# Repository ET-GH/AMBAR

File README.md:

# AMBAR
The software and hardware of the AMBAR project

Utilized Firmware includes all the logic used for our system.

Measurement & Control includes logic and API used for the measurement and control of the system. Airbrake.c includes references to a tmc5240 driver. Utilized Firmware has the completed driver but if your system used something else then changes must be made in the airbrake logic.

Communication includes logic and api used for communication and data between the flight computer and ground station. radio_bridge includes references to an sx1280 driver. Utilized Firmware has the completed driver but if your system used something else then changes must be made in the bridge logic. usb_comm includes references to the STM32 USB drivers. Utilized Firmware has the completed driver but if your system used something else then changes must be made in the usb logic.

GroundStation includes all the files used for qt application. Qt libraries were used for each of the integration files. The architecture can still be used if you don't want to use QT but the function calls will not work without the installed QT libraries.

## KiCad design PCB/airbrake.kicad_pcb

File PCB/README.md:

# AMBAR Flight Computer PCB
What we used for our project. You can buy all the components off of JLCPCB and Digikey

Export the gerber files and the bill of materials. Purchase the electrical componetns from digikey if you plan to solder but it's much easier to simply ask JLCPCB to fabricate and assemble the board.

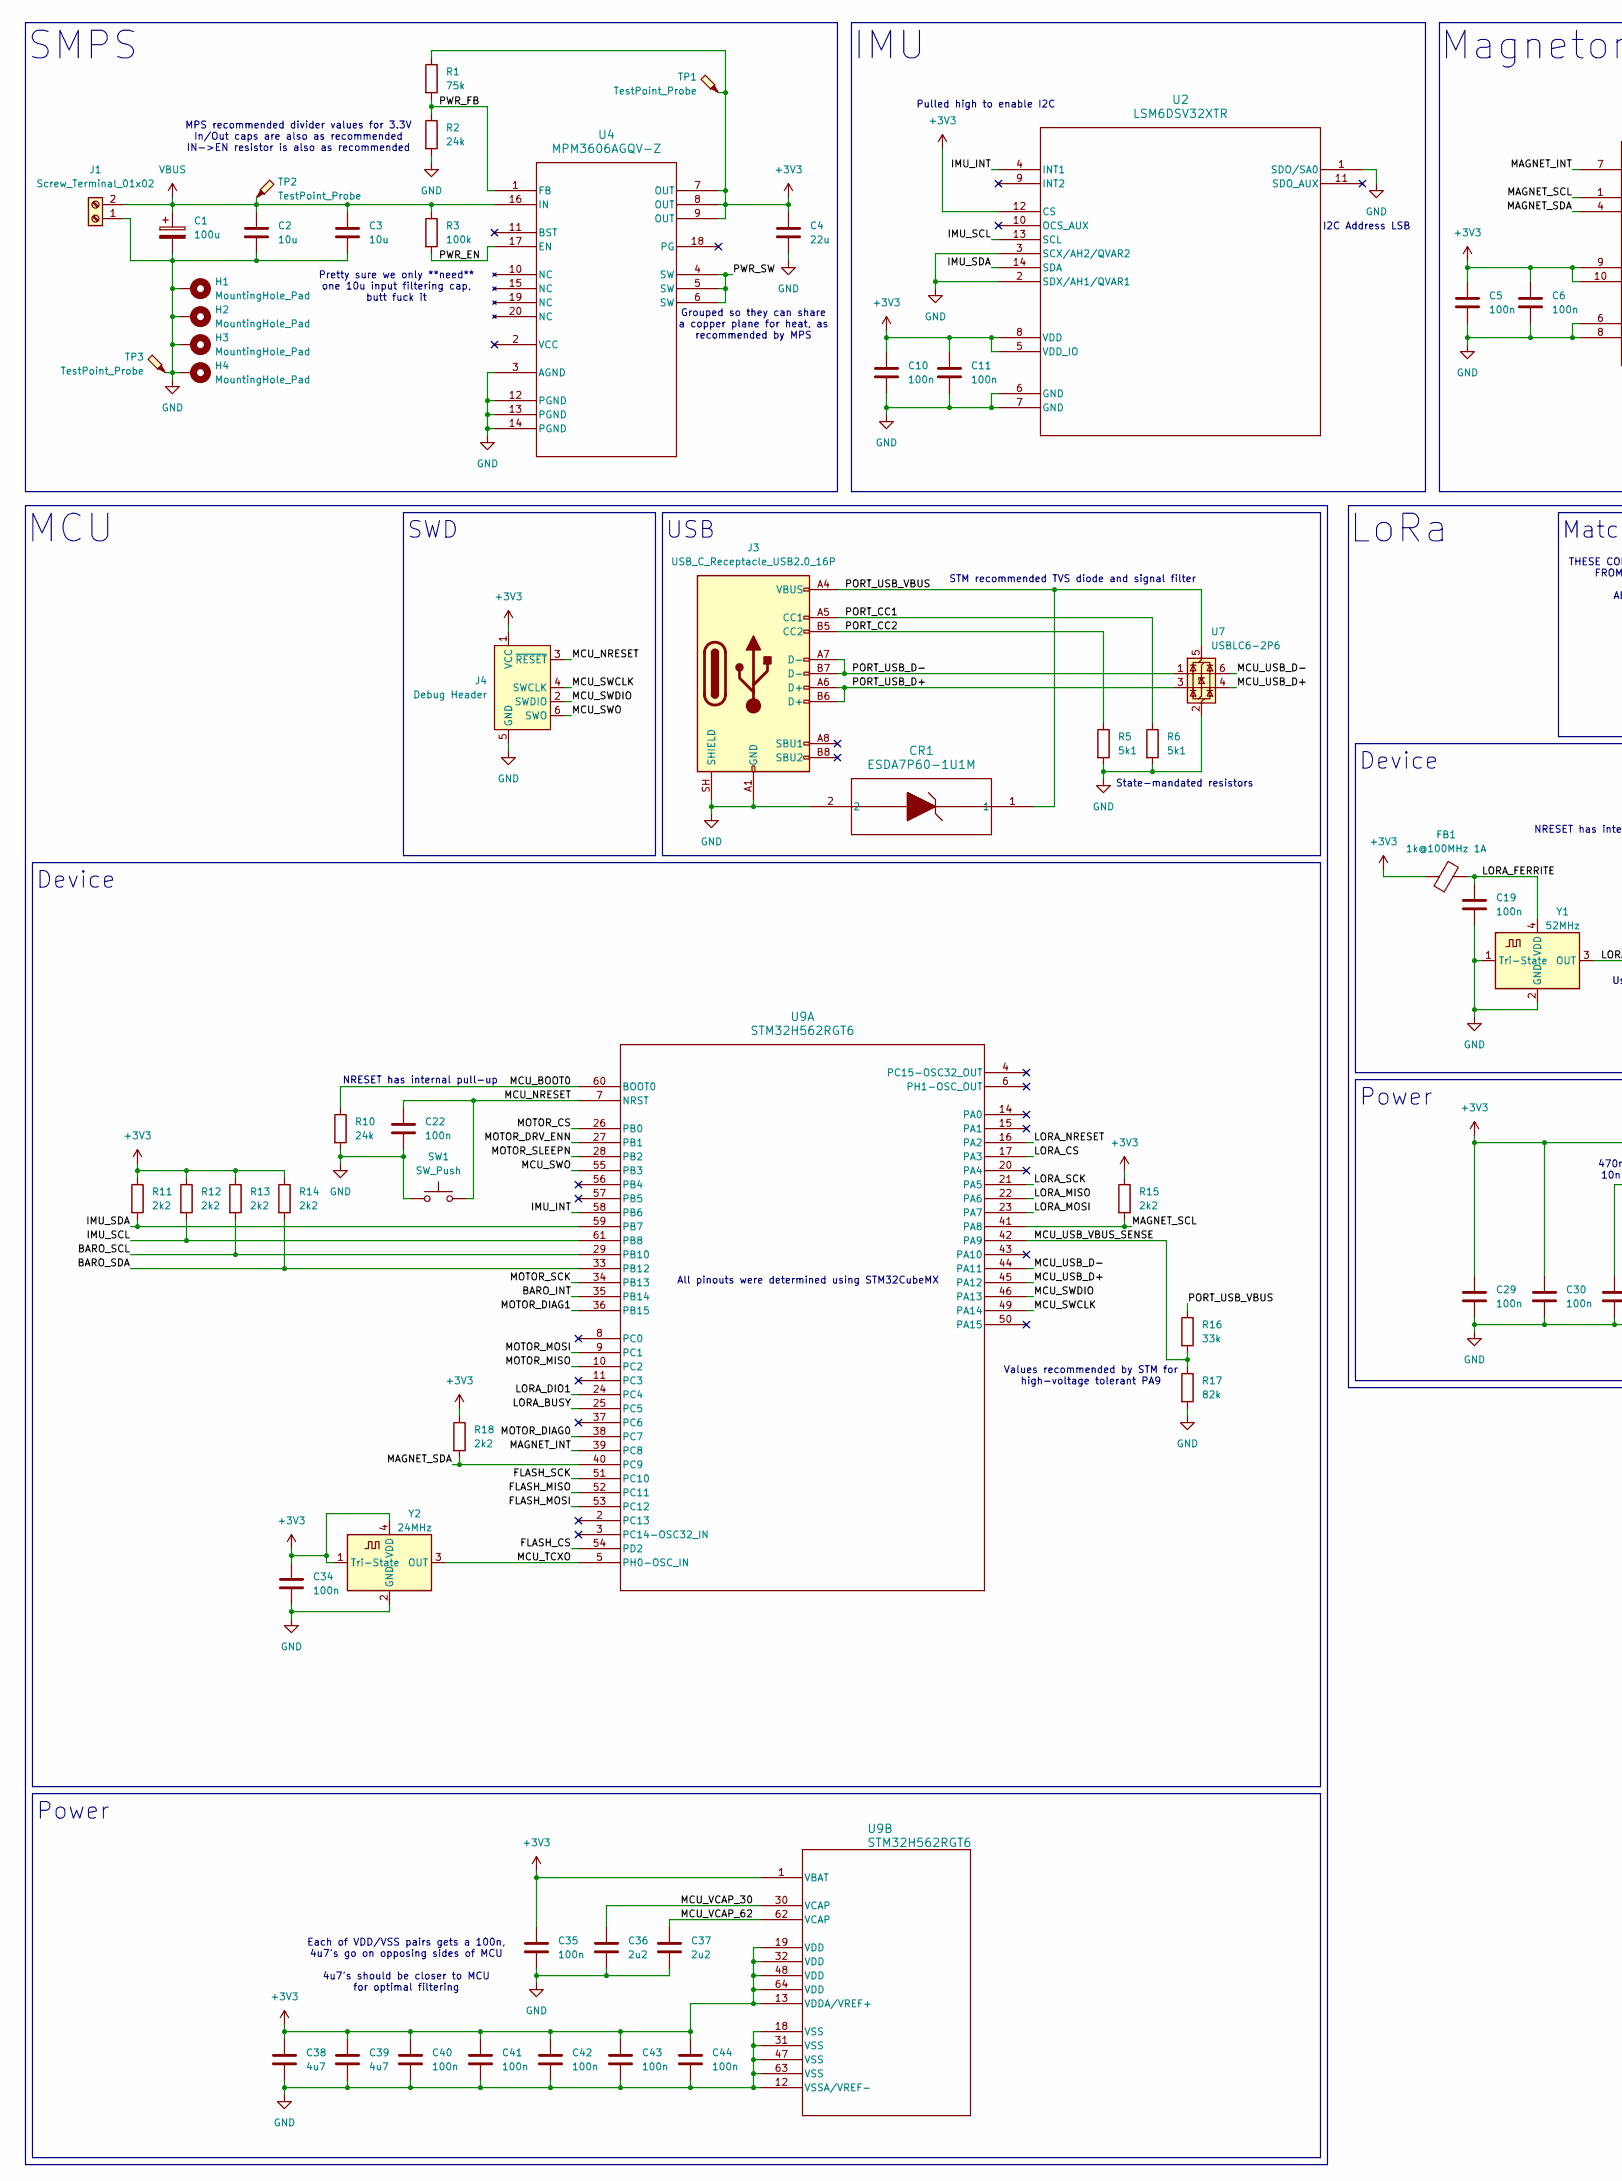
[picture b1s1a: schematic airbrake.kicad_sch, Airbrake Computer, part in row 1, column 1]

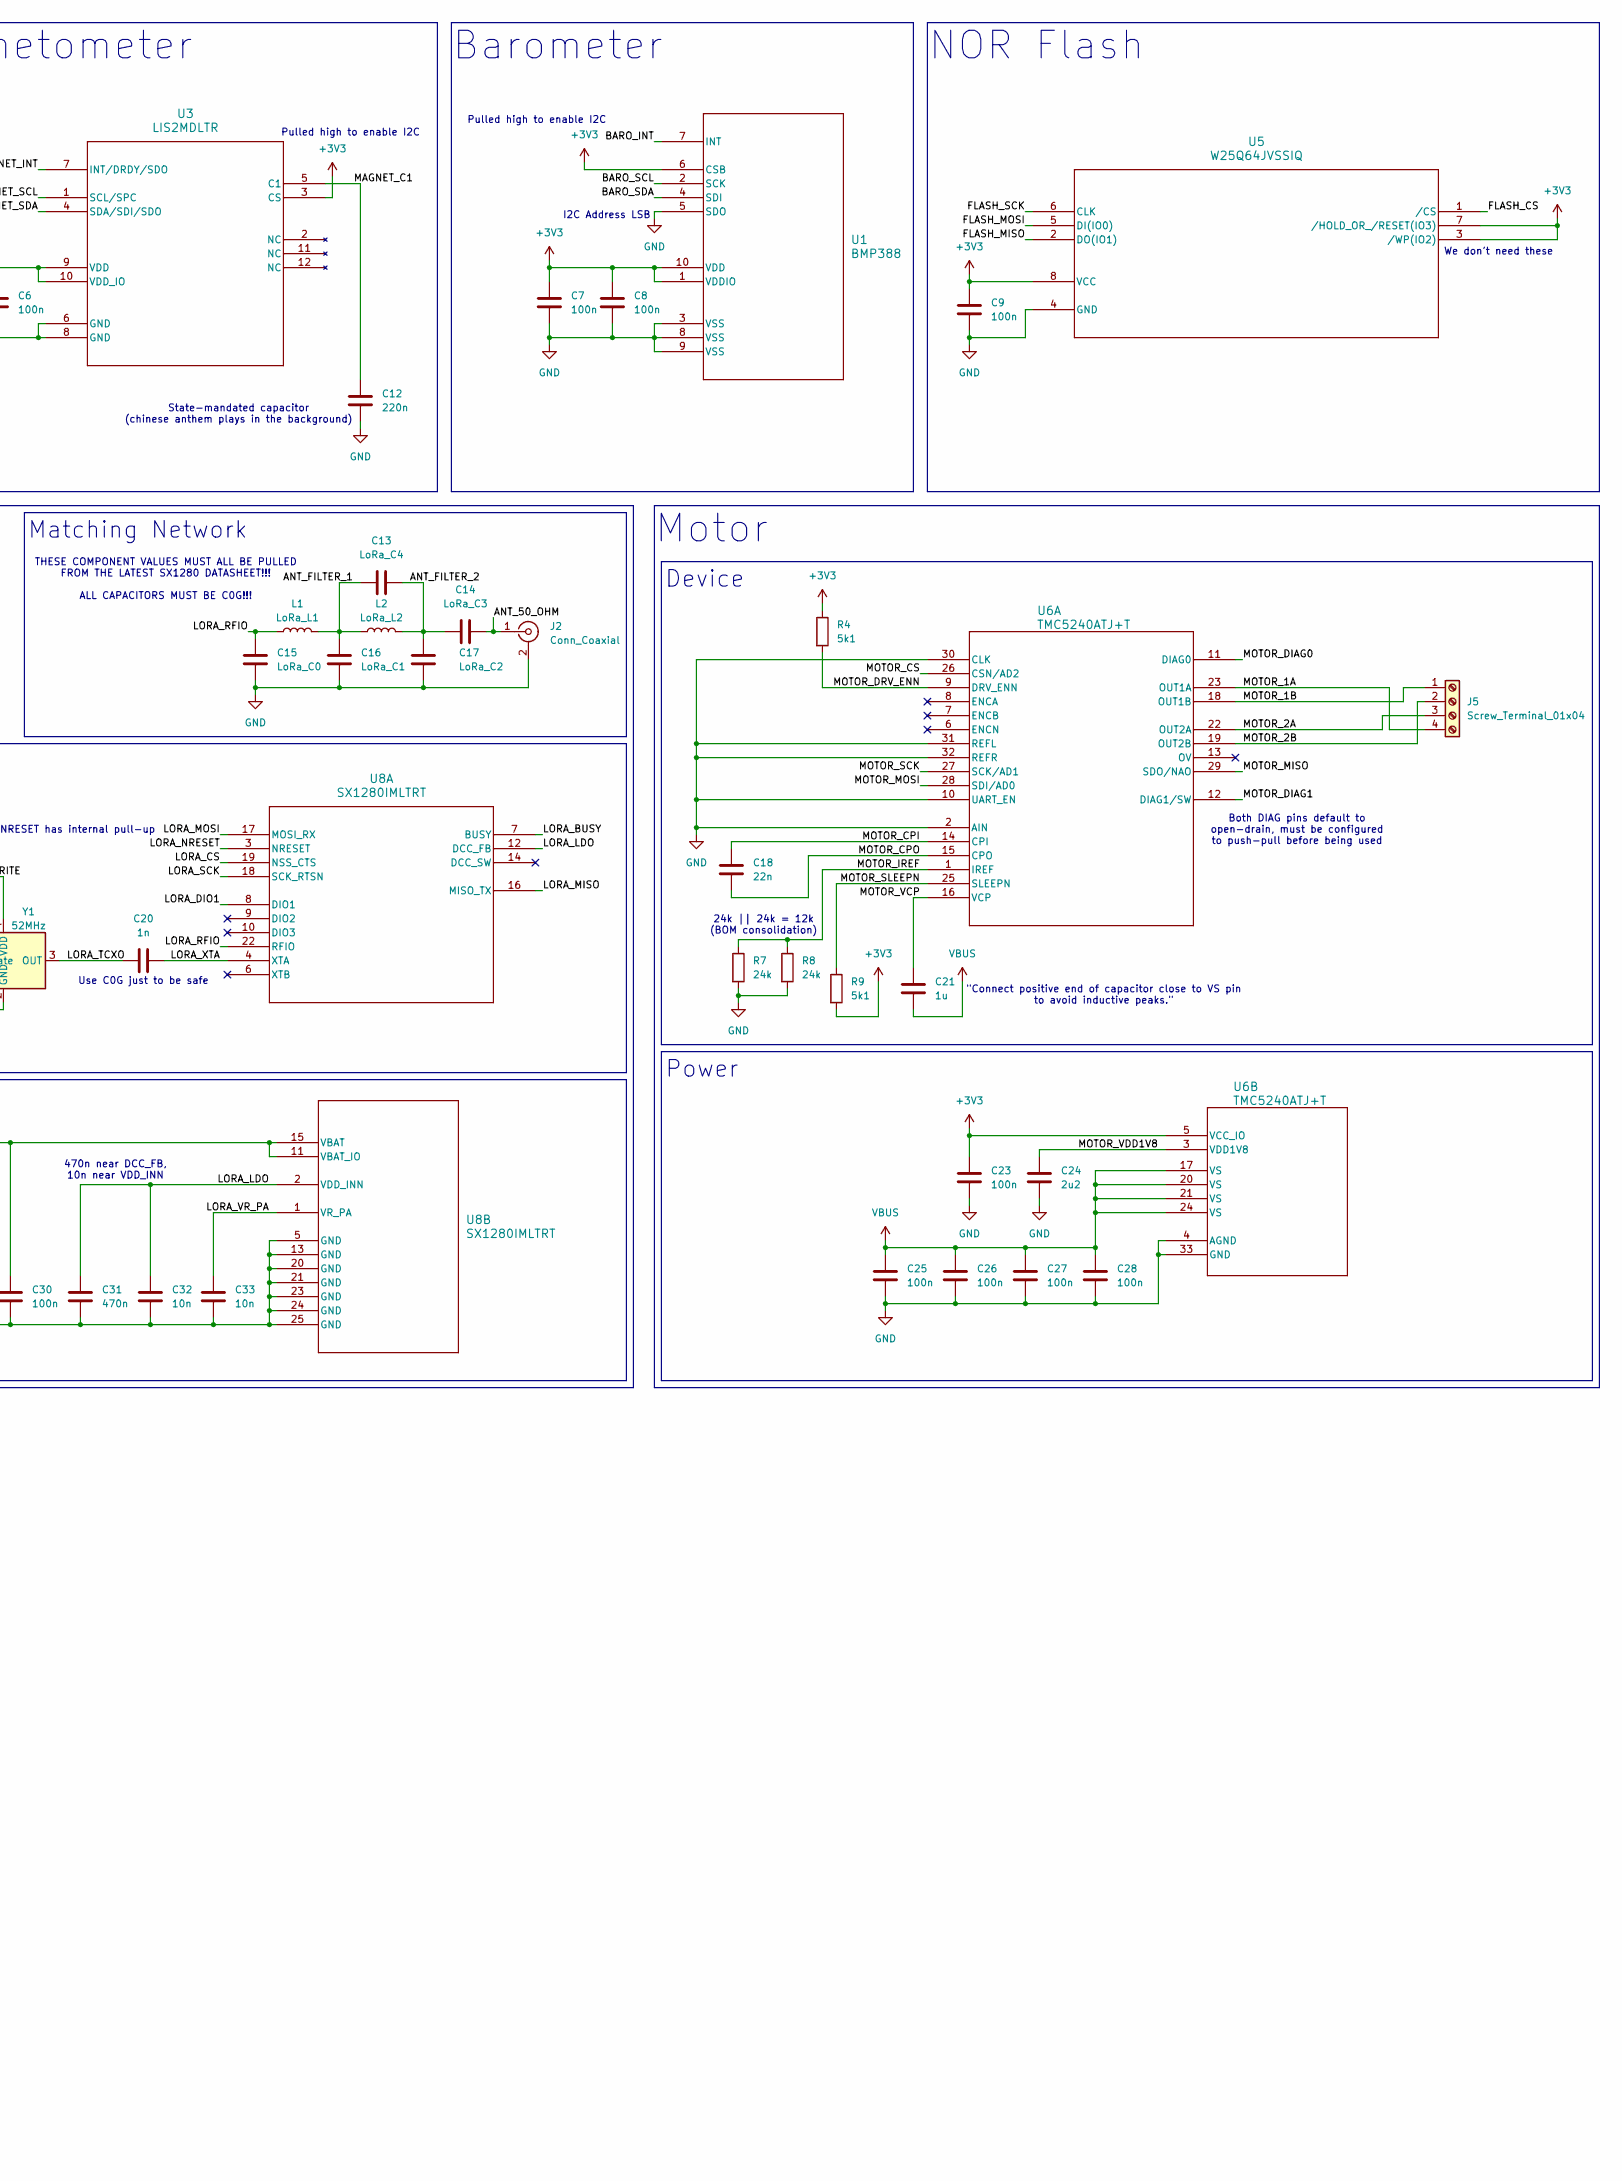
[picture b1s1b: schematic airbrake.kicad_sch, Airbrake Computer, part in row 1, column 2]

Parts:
C1: 100u; CP_Elec_6.3x7.7
C2, C3: 10u; C_0603_1608Metric
C4: 22u; C_0603_1608Metric
C5, C6, C7, C8, C9, C10, C11, C19, C22, C23, C25, C26, C27, C28, C29, C30, C34, C35, C40, C41, C42, C43, C44: 100n; C_0402_1005Metric
C12: 220n; C_0402_1005Metric
C13: LoRa_C4; C_0402_1005Metric
C14: LoRa_C3; C_0402_1005Metric
C15: LoRa_C0; C_0402_1005Metric
C16: LoRa_C1; C_0402_1005Metric
C17: LoRa_C2; C_0402_1005Metric
C18: 22n; C_0402_1005Metric
C20: 1n; C_0402_1005Metric
C21: 1u; C_0402_1005Metric
C24, C36, C37: 2u2; C_0402_1005Metric
C31: 470n; C_0402_1005Metric
C32, C33: 10n; C_0402_1005Metric
C38, C39: 4u7; C_0402_1005Metric
CR1: ESDA7P60-1U1M; ZDO_1610_STM
FB1: 1k@100MHz 1A; L_0603_1608Metric
H1, H2, H3, H4: MountingHole_Pad; MountingHole_2.2mm_M2_Pad_Via
J1: Screw_Terminal_01x02; TerminalBlock_Xinya_XY308-2.54-2P_1x02_P2.54mm_Horizontal
J2: Conn_Coaxial; U.FL_Hirose_U.FL-R-SMT-1_Vertical
J3: USB_C_Receptacle_USB2.0_16P; USB_C_Receptacle_GCT_USB4105-xx-A_16P_TopMnt_Horizontal
J4: Debug Header; Tag-Connect_TC2030-IDC-NL_2x03_P1.27mm_Vertical
J5: Screw_Terminal_01x04; TerminalBlock_Xinya_XY308-2.54-4P_1x04_P2.54mm_Horizontal
L1: LoRa_L1; L_0402_1005Metric
L2: LoRa_L2; L_0402_1005Metric
R1: 75k; R_0402_1005Metric
R2, R7, R8, R10: 24k; R_0402_1005Metric
R3: 100k; R_0402_1005Metric
R4, R5, R6, R9: 5k1; R_0402_1005Metric
R11, R12, R13, R14, R15, R18: 2k2; R_0402_1005Metric
R16: 33k; R_0402_1005Metric
R17: 82k; R_0402_1005Metric
SW1: SW_Push; SW_SPST_B3U-1000P
TP1, TP2, TP3: TestPoint_Probe; TestPoint_Pad_D2.5mm
U1: BMP388; QFN_BMP388_BOS
U2: LSM6DSV32XTR; LGA-14L_2p5X3p0X0p86_STM
U3: LIS2MDLTR; LGA-12_2X2X1_STM
U4: MPM3606AGQV-Z; QFN3p0x5p0x1p6_MPM3606A_MNP
U5: W25Q64JVSSIQ; SOIC-8_5P28X5P28_WIN-L
U6: TMC5240ATJ+T; 21-0140_T3255&plus_5C_ADI-L
U7: USBLC6-2P6; SOT-666
U8: SX1280IMLTRT; QFN24_4X4_SEM-L
U9: STM32H562RGT6; LQFP64-10x10mm_STM
Y1: 52MHz; Crystal_SMD_2016-4Pin_2.0x1.6mm
Y2: 24MHz; Crystal_SMD_2520-4Pin_2.5x2.0mm

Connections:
+3V3: C4.1, C5.1, C6.1, C7.1, C8.1, C9.1, C10.1, C11.1, C23.1, C29.1, C30.1, C34.1, C35.1, C38.1, C39.1, C40.1, C41.1, C42.1, C43.1, C44.1, FB1.1, J4.1 (VCC), R1.1, R4.1, R9.2, R11.1, R12.1, R13.1, R14.1, R15.1, R18.1, TP1.1 (1_1), U1.1 (VDDIO), U1.6 (CSB), U1.10 (VDD), U2.5 (VDD_IO), U2.8 (VDD), U2.12 (CS), U3.3 (CS), U3.9 (VDD), U3.10 (VDD_IO), U4.7 (OUT), U4.8 (OUT), U4.9 (OUT), U5.3 (/WP(IO2)), U5.7 (/HOLD_OR_/RESET(IO3)), U5.8 (VCC), U6.5 (VCC_IO), U8.11 (VBAT_IO), U8.15 (VBAT), U9.1 (VBAT), U9.13 (VDDA/VREF+), U9.19 (VDD), U9.32 (VDD), U9.48 (VDD), U9.64 (VDD), Y2.1 (Tri-State), Y2.4 (VDD)
/ANT_50_OHM: C14.2, J2.1 (In)
/ANT_FILTER_1: C13.1, C16.1, L1.2, L2.1
/ANT_FILTER_2: C13.2, C14.1, C17.1, L2.2
/BARO_INT: U1.7 (INT), U9.35 (PB14)
/BARO_SCL: R13.2, U1.2 (SCK), U9.29 (PB10)
/BARO_SDA: R14.2, U1.4 (SDI), U9.33 (PB12)
/FLASH_CS: U5.1 (/CS), U9.54 (PD2)
/FLASH_MISO: U5.2 (DO(IO1)), U9.52 (PC11)
/FLASH_MOSI: U5.5 (DI(IO0)), U9.53 (PC12)
/FLASH_SCK: U5.6 (CLK), U9.51 (PC10)
/IMU_INT: U2.4 (INT1), U9.58 (PB6)
/IMU_SCL: R12.2, U2.13 (SCL), U9.61 (PB8)
/IMU_SDA: R11.2, U2.14 (SDA), U9.59 (PB7)
/LORA_BUSY: U8.7 (BUSY), U9.25 (PC5)
/LORA_CS: U8.19 (NSS_CTS), U9.17 (PA3)
/LORA_DIO1: U8.8 (DIO1), U9.24 (PC4)
/LORA_FERRITE: C19.1, FB1.2, Y1.4 (VDD)
/LORA_LDO: C31.1, C32.1, U8.2 (VDD_INN), U8.12 (DCC_FB)
/LORA_MISO: U8.16 (MISO_TX), U9.22 (PA6)
/LORA_MOSI: U8.17 (MOSI_RX), U9.23 (PA7)
/LORA_NRESET: U8.3 (NRESET), U9.16 (PA2)
/LORA_RFIO: C15.1, L1.1, U8.22 (RFIO)
/LORA_SCK: U8.18 (SCK_RTSN), U9.21 (PA5)
/LORA_TCXO: C20.1, Y1.3 (OUT)
/LORA_VR_PA: C33.1, U8.1 (VR_PA)
/LORA_XTA: C20.2, U8.4 (XTA)
/MAGNET_C1: C12.1, U3.5 (C1)
/MAGNET_INT: U3.7 (INT/DRDY/SDO), U9.39 (PC8)
/MAGNET_SCL: R15.2, U3.1 (SCL/SPC), U9.41 (PA8)
/MAGNET_SDA: R18.2, U3.4 (SDA/SDI/SDO), U9.40 (PC9)
/MCU_BOOT0: R10.1, U9.60 (BOOT0)
/MCU_NRESET: C22.1, J4.3 (~RESET), SW1.2, U9.7 (NRST)
/MCU_SWCLK: J4.4 (SWCLK), U9.49 (PA14)
/MCU_SWDIO: J4.2 (SWDIO), U9.46 (PA13)
/MCU_SWO: J4.6 (SWO), U9.55 (PB3)
/MCU_TCXO: U9.5 (PH0-OSC_IN), Y2.3 (OUT)
/MCU_USB_D+: U7.4 (I/O2), U9.45 (PA12)
/MCU_USB_D-: U7.6 (I/O1), U9.44 (PA11)
/MCU_USB_VBUS_SENSE: R16.2, R17.1, U9.42 (PA9)
/MCU_VCAP_30: C36.1, U9.30 (VCAP)
/MCU_VCAP_62: C37.1, U9.62 (VCAP)
/MOTOR_1A: J5.4, U6.23 (OUT1A)
/MOTOR_1B: J5.1, U6.18 (OUT1B)
/MOTOR_2A: J5.3, U6.22 (OUT2A)
/MOTOR_2B: J5.2, U6.19 (OUT2B)
/MOTOR_CPI: C18.1, U6.14 (CPI)
/MOTOR_CPO: C18.2, U6.15 (CPO)
/MOTOR_CS: U6.26 (CSN/AD2), U9.26 (PB0)
/MOTOR_DIAG0: U6.11 (DIAG0), U9.38 (PC7)
/MOTOR_DIAG1: U6.12 (DIAG1/SW), U9.36 (PB15)
/MOTOR_DRV_ENN: R4.2, U6.9 (DRV_ENN), U9.27 (PB1)
/MOTOR_IREF: R7.1, R8.1, U6.1 (IREF)
/MOTOR_MISO: U6.29 (SDO/NAO), U9.10 (PC2)
/MOTOR_MOSI: U6.28 (SDI/AD0), U9.9 (PC1)
/MOTOR_SCK: U6.27 (SCK/AD1), U9.34 (PB13)
/MOTOR_SLEEPN: R9.1, U6.25 (SLEEPN), U9.28 (PB2)
/MOTOR_VCP: C21.1, U6.16 (VCP)
/MOTOR_VDD1V8: C24.1, U6.3 (VDD1V8)
/PORT_CC1: J3.A5 (CC1), R6.1
/PORT_CC2: J3.B5 (CC2), R5.1
/PORT_USB_D+: J3.A6 (D+), J3.B6 (D+), U7.3 (I/O2)
/PORT_USB_D-: J3.A7 (D-), J3.B7 (D-), U7.1 (I/O1)
/PORT_USB_VBUS: CR1.1, J3.A4 (VBUS), J3.A9 (VBUS), J3.B4 (VBUS), J3.B9 (VBUS), R16.1, U7.5 (VBUS)
/PWR_EN: R3.2, U4.17 (EN)
/PWR_FB: R1.2, R2.1, U4.1 (FB)
/PWR_SW: U4.4 (SW), U4.5 (SW), U4.6 (SW)
GND: C1.2, C2.2, C3.2, C4.2, C5.2, C6.2, C7.2, C8.2, C9.2, C10.2, C11.2, C12.2, C15.2, C16.2, C17.2, C19.2, C22.2, C23.2, C24.2, C25.2, C26.2, C27.2, C28.2, C29.2, C30.2, C31.2, C32.2, C33.2, C34.2, C35.2, C36.2, C37.2, C38.2, C39.2, C40.2, C41.2, C42.2, C43.2, C44.2, CR1.2, H1.1 (1_1), H2.1 (1_1), H3.1 (1_1), H4.1 (1_1), J1.1, J2.2 (Ext), J3.A1 (GND), J3.A12 (GND), J3.B1 (GND), J3.B12 (GND), J3.SH (SHIELD), J4.5 (GND), R2.2, R5.2, R6.2, R7.2, R8.2, R10.2, R17.2, SW1.1, TP3.1 (1_1), U1.3 (VSS), U1.5 (SDO), U1.8 (VSS), U1.9 (VSS), U2.1 (SDO/SA0), U2.2 (SDX/AH1/QVAR1), U2.3 (SCX/AH2/QVAR2), U2.6 (GND), U2.7 (GND), U3.6 (GND), U3.8 (GND), U4.3 (AGND), U4.12 (PGND), U4.13 (PGND), U4.14 (PGND), U5.4 (GND), U6.2 (AIN), U6.4 (AGND), U6.10 (UART_EN), U6.30 (CLK), U6.31 (REFL), U6.32 (REFR), U6.33 (GND), U7.2 (GND), U8.5 (GND), U8.13 (GND), U8.20 (GND), U8.21 (GND), U8.23 (GND), U8.24 (GND), U8.25 (GND), U9.12 (VSSA/VREF-), U9.18 (VSS), U9.31 (VSS), U9.47 (VSS), U9.63 (VSS), Y1.1 (Tri-State), Y1.2 (GND), Y2.2 (GND)
VBUS: C1.1, C2.1, C3.1, C21.2, C25.1, C26.1, C27.1, C28.1, J1.2, R3.1, TP2.1 (1_1), U4.16 (IN), U6.17 (VS), U6.20 (VS), U6.21 (VS), U6.24 (VS)

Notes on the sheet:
MCU
NRESET has internal pull-up
Pulled high to enable I2C
Each of VDD/VSS pairs gets a 100n, 4u7's go on opposing sides of MCU 4u7's should be closer to MCU for optimal filtering
Values recommended by STM for high-voltage tolerant PA9
State-mandated resistors
All pinouts were determined using STM32CubeMX
Motor
SMPS
Power
Device
I2C Address LSB
Use C0G just to be safe
Barometer
Matching Network
470n near DCC_FB, 10n near VDD_INN
NOR Flash
24k || 24k = 12k (BOM consolidation)
Both DIAG pins default to open-drain, must be configured to push-pull before being used
SWD
LoRa
MPS recommended divider values for 3.3V In/Out caps are also as recommended IN->EN resistor is also as recommended
IMU
Grouped so they can share a copper plane for heat, as recommended by MPS
Magnetometer
"Connect positive end of capacitor close to VS pin to avoid inductive peaks."
USB
State-mandated capacitor (chinese anthem plays in the background)
THESE COMPONENT VALUES MUST ALL BE PULLED FROM THE LATEST SX1280 DATASHEET!!! ALL CAPACITORS MUST BE C0G!!!
We don't need these
Pretty sure we only **need** one 10u input filtering cap, butt fuck it
STM recommended TVS diode and signal filter

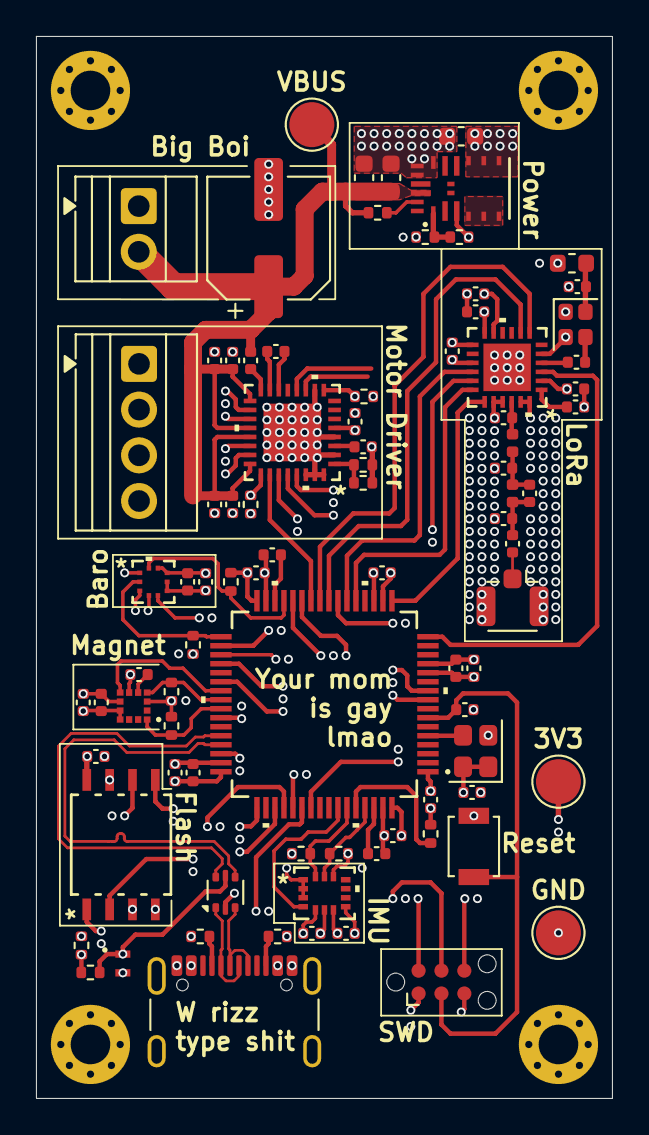
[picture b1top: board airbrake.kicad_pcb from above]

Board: 6 copper layers, 32.0 x 59.0 mm, 90 parts (0 on the bottom side), 69 nets.

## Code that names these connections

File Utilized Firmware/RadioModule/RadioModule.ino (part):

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#include <string.h>
#include "rocket_protocol.h"

#define LORA_SCK 5
#define LORA_MISO 3
#define LORA_MOSI 6
#define LORA_CS 7
#define LORA_RST 8
#define LORA_DIO1 9
#define LORA_BUSY 36
#define LORA_TXEN 10
#define LORA_RXEN 21

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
